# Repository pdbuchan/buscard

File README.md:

# BusCard Project

The illustrated project description is available on the [BusCard GitHub Pages website](https://pdbuchan.github.io/buscard/).

This repository documents information on the BusCard, an IEEE-488 and parallel printer interface for the Commodore 64. The BusCard, and subsequent BusCard II, were manufactured by Batteries Included Ltd. of Toronto, Canada. On my BusCard, the circuit board is labeled "Rev A" and "1983". I used it to provide IEEE-488 functionality to my Commodore 64 in order to use a 4040 disk drive and 8023P printer. It also provides BASIC 4.0 and comes with an assembler and disassembler.

Unlike the BusCard II, the BusCard does not contain any proprietary integrated circuits. As a result, I was able to successfully reverse-engineer it and produce an exact working duplicate. I used EAGLE CAD software for the schematic and circuit board design. All information required to produce it is provided. If you would like to build it, you can send the GERBER files provided here to the manufacturer of your choice. You would only need EAGLE if you wish to change the board layout or circuit.

## License

All of my photographs and EAGLE files are released under [Creative Commons License CC BY-SA](https://creativecommons.org/licenses/by-sa/4.0/). The original BusCard, EPROM content, and user manual are copyright Batteries Included Ltd.

## Repository layout

```text
buscard/
├── README.md
└── docs/
    ├── README.md
    ├── index.html
    ├── .nojekyll
    └── assets/
        ├── buscard.css
        ├── buscard_rev_a_manual.pdf
        ├── schematic.pdf
        ├── cam/
        │   ├── README.md
        │   └── elecrow-gerb274x.cam
        ├── datasheets/
        │   ├── README.md
        │   ├── datasheets.html
        │   ├── 1N4148.pdf
        │   ├── 2N3904.pdf
        │   ├── 2N4401.pdf
        │   ├── 74LS00N.pdf
        │   ├── 74LS04N.pdf
        │   ├── 74LS08N.pdf
        │   ├── 74LS139N.pdf
        │   ├── 74LS21N.pdf
        │   ├── 74LS32N.pdf
        │   ├── 75160B.pdf
        │   ├── 75161B.pdf
        │   ├── 8255AC-5.pdf
        │   ├── 82C55A.pdf
        │   ├── 8-SPST-DIP-Switch.pdf
        │   ├── CK05BX104K.pdf
        │   ├── clip_cable.pdf
        │   ├── clip_receptacle.pdf
        │   ├── female-edge-connector.pdf
        │   ├── micro_clip.pdf
        │   ├── resistor-network.pdf
        │   ├── resistors.pdf
        │   ├── shunt.pdf
        │   └── TMS2564.pdf
        ├── drawings/
        │   ├── README.md
        │   ├── buscard_dimensions.pdf
        │   ├── buscard_dimensions.vsdx
        │   ├── buscard_expansion_port.pdf
        │   ├── buscard_expansion_port.vsdx
        │   ├── buscard_IEEE-488_port.pdf
        │   ├── buscard_IEEE-488_port.vsdx
        │   ├── buscard_parallel_port.pdf
        │   ├── buscard_parallel_port.vsdx
        │   ├── buscard_parts_layout.pdf
        │   ├── buscard_parts_layout.vsdx
        │   ├── buscard_schematic.pdf
        │   ├── new_buscard_dimensions.pdf
        │   └── new_buscard_dimensions.vsdx
        ├── eagle/
        │   ├── README.md
        │   ├── buscard.brd
        │   └── buscard.sch
        ├── eprom/
        │   ├── README.md
        │   ├── buscardv0.9-tms2564.html
        │   ├── buscard_u1_rom_discussion.html
        │   ├── additional-sockets-u13-u14-u15.html
        │   ├── burning_TMS2564_EPROM.docx
        │   ├── burning_TMS2564_EPROM.pdf
        │   ├── buscard_u1_6502_annotated_listing.txt
        │   ├── buscard_u1_rom_discussion.md
        │   ├── additional-sockets-u13-u14-u15.md
        │   └── buscardv0.9-tms2564.bin
        ├── gerber/
        │   ├── README.md
        │   ├── gerber.html
        │   ├── buscard.GBL
        │   ├── buscard.GBO
        │   ├── buscard.GBS
        │   ├── buscard.GML
        │   ├── buscard.GTL
        │   ├── buscard.GTO
        │   ├── buscard.GTS
        │   ├── buscard.TXT
        │   ├── PLEASE_CHAMFER_CARD_EDGES.jpg
        │   └── PLEASE_CONTACT_ME_ABOUT_GOLD_FINGERS.txt
        ├── images/
        │   ├── README.md
        │   ├── orig_gallery.html
        │   ├── new_gallery.html
        │   ├── bottom_cover_inside.jpg
        │   ├── bottom_cover_inside_thumb.jpg
        │   ├── bottom_cover_underside.jpg
        │   ├── bottom_cover_underside_thumb.jpg
        │   ├── bottom.jpg
        │   ├── bottom_of_board_backlit.jpg
        │   ├── bottom_of_board_backlit_thumb.jpg
        │   ├── bottom_thumb.jpg
        │   ├── clips.jpg
        │   ├── clips_thumb.jpg
        │   ├── diodes.jpg
        │   ├── diodes-switch_foil_backlit_top.jpg
        │   ├── diodes-switch_foil_backlit_top_thumb.jpg
        │   ├── diodes-switch_foil_top.jpg
        │   ├── diodes-switch_foil_top_thumb.jpg
        │   ├── diodes_thumb.jpg
        │   ├── expansion_port_backlit1.jpg
        │   ├── expansion_port_backlit1_thumb.jpg
        │   ├── expansion_port_backlit2.jpg
        │   ├── expansion_port_backlit2_thumb.jpg
        │   ├── new_bottom.jpg
        │   ├── new_bottom_thumb.jpg
        │   ├── new_top1.jpg
        │   ├── new_top1_thumb.jpg
        │   ├── new_top2.jpg
        │   ├── new_top2_thumb.jpg
        │   ├── new_top_no_chips1.jpg
        │   ├── new_top_no_chips1_thumb.jpg
        │   ├── new_top_no_chips2.jpg
        │   ├── new_top_no_chips2_thumb.jpg
        │   ├── not_plugged_in.jpg
        │   ├── not_plugged_in_thumb.jpg
        │   ├── photo_buscard_board_bottom_r0.jpg
        │   ├── photo_buscard_board_top_r0.jpg
        │   ├── plugged_in.jpg
        │   ├── plugged_in_thumb.jpg
        │   ├── side_view01.jpg
        │   ├── side_view01_thumb.jpg
        │   ├── side_view02.jpg
        │   ├── side_view02_thumb.jpg
        │   ├── side_view03.jpg
        │   ├── side_view03_thumb.jpg
        │   ├── side_view04.jpg
        │   ├── side_view04_thumb.jpg
        │   ├── side_view05.jpg
        │   ├── side_view05_thumb.jpg
        │   ├── side_view06.jpg
        │   ├── side_view06_thumb.jpg
        │   ├── side_view07.jpg
        │   ├── side_view07_thumb.jpg
        │   ├── side_view08.jpg
        │   ├── side_view08_thumb.jpg
        │   ├── side_view09.jpg
        │   ├── side_view09_thumb.jpg
        │   ├── side_view10.jpg
        │   ├── side_view10_thumb.jpg
        │   ├── side_view11.jpg
        │   ├── side_view11_thumb.jpg
        │   ├── side_view12.jpg
        │   ├── side_view12_thumb.jpg
        │   ├── side_view13.jpg
        │   ├── side_view13_thumb.jpg
        │   ├── top_cover_inside.jpg
        │   ├── top_cover_inside_thumb.jpg
        │   ├── top_foil1.jpg
        │   ├── top_foil1_thumb.jpg
        │   ├── top_no_covers1.jpg
        │   ├── top_no_covers1_thumb.jpg
        │   ├── top_no_covers2.jpg
        │   ├── top_no_covers2_thumb.jpg
        │   ├── top_of_board_backlit.jpg
        │   ├── top_of_board_backlit_thumb.jpg
        │   ├── top_with_bottom_cover1.jpg
        │   ├── top_with_bottom_cover1_thumb.jpg
        │   ├── top_with_bottom_cover2.jpg
        │   ├── top_with_bottom_cover2_thumb.jpg
        │   ├── top_with_cover1.jpg
        │   ├── top_with_cover1_thumb.jpg
        │   ├── top_with_cover2.jpg
        │   └── top_with_cover2_thumb.jpg
        ├── libraries/
        │   ├── README.md
        │   ├── libraries.html
        │   ├── 1N4148.lbr
        │   ├── 2564.lbr
        │   ├── 2N3904_and_2N4401.lbr
        │   ├── 74LS00N.lbr
        │   ├── 74LS04N.lbr
        │   ├── 74LS08N.lbr
        │   ├── 74LS139N.lbr
        │   ├── 74LS21N.lbr
        │   ├── 74LS32N.lbr
        │   ├── 75160AN.lbr
        │   ├── 75161AN.lbr
        │   ├── 8255AC-5.lbr
        │   ├── capacitor-CK05BX104K.lbr
        │   ├── clip-header-MTA02-100.lbr
        │   ├── commodore-card-edges.lbr
        │   ├── dip-switch-DS08.lbr
        │   ├── female-44-pin-edge-connector.lbr
        │   ├── frame.lbr
        │   ├── jumper-header-3.lbr
        │   ├── mystery_plug-MTA04-100.lbr
        │   ├── resistor.lbr
        │   └── resistor-network-sil-G09R.lbr
        └── parts/
            ├── README.md
            ├── new_buscard_bom.xlsx
            └── orig_buscard_parts.xlsx
```

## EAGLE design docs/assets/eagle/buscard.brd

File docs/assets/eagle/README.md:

# EAGLE board and schematic files

| File | Description |
|---|---|
| `buscard.brd` | EAGLE printed circuit board file |
| `buscard.sch` | EAGLE schematic file |

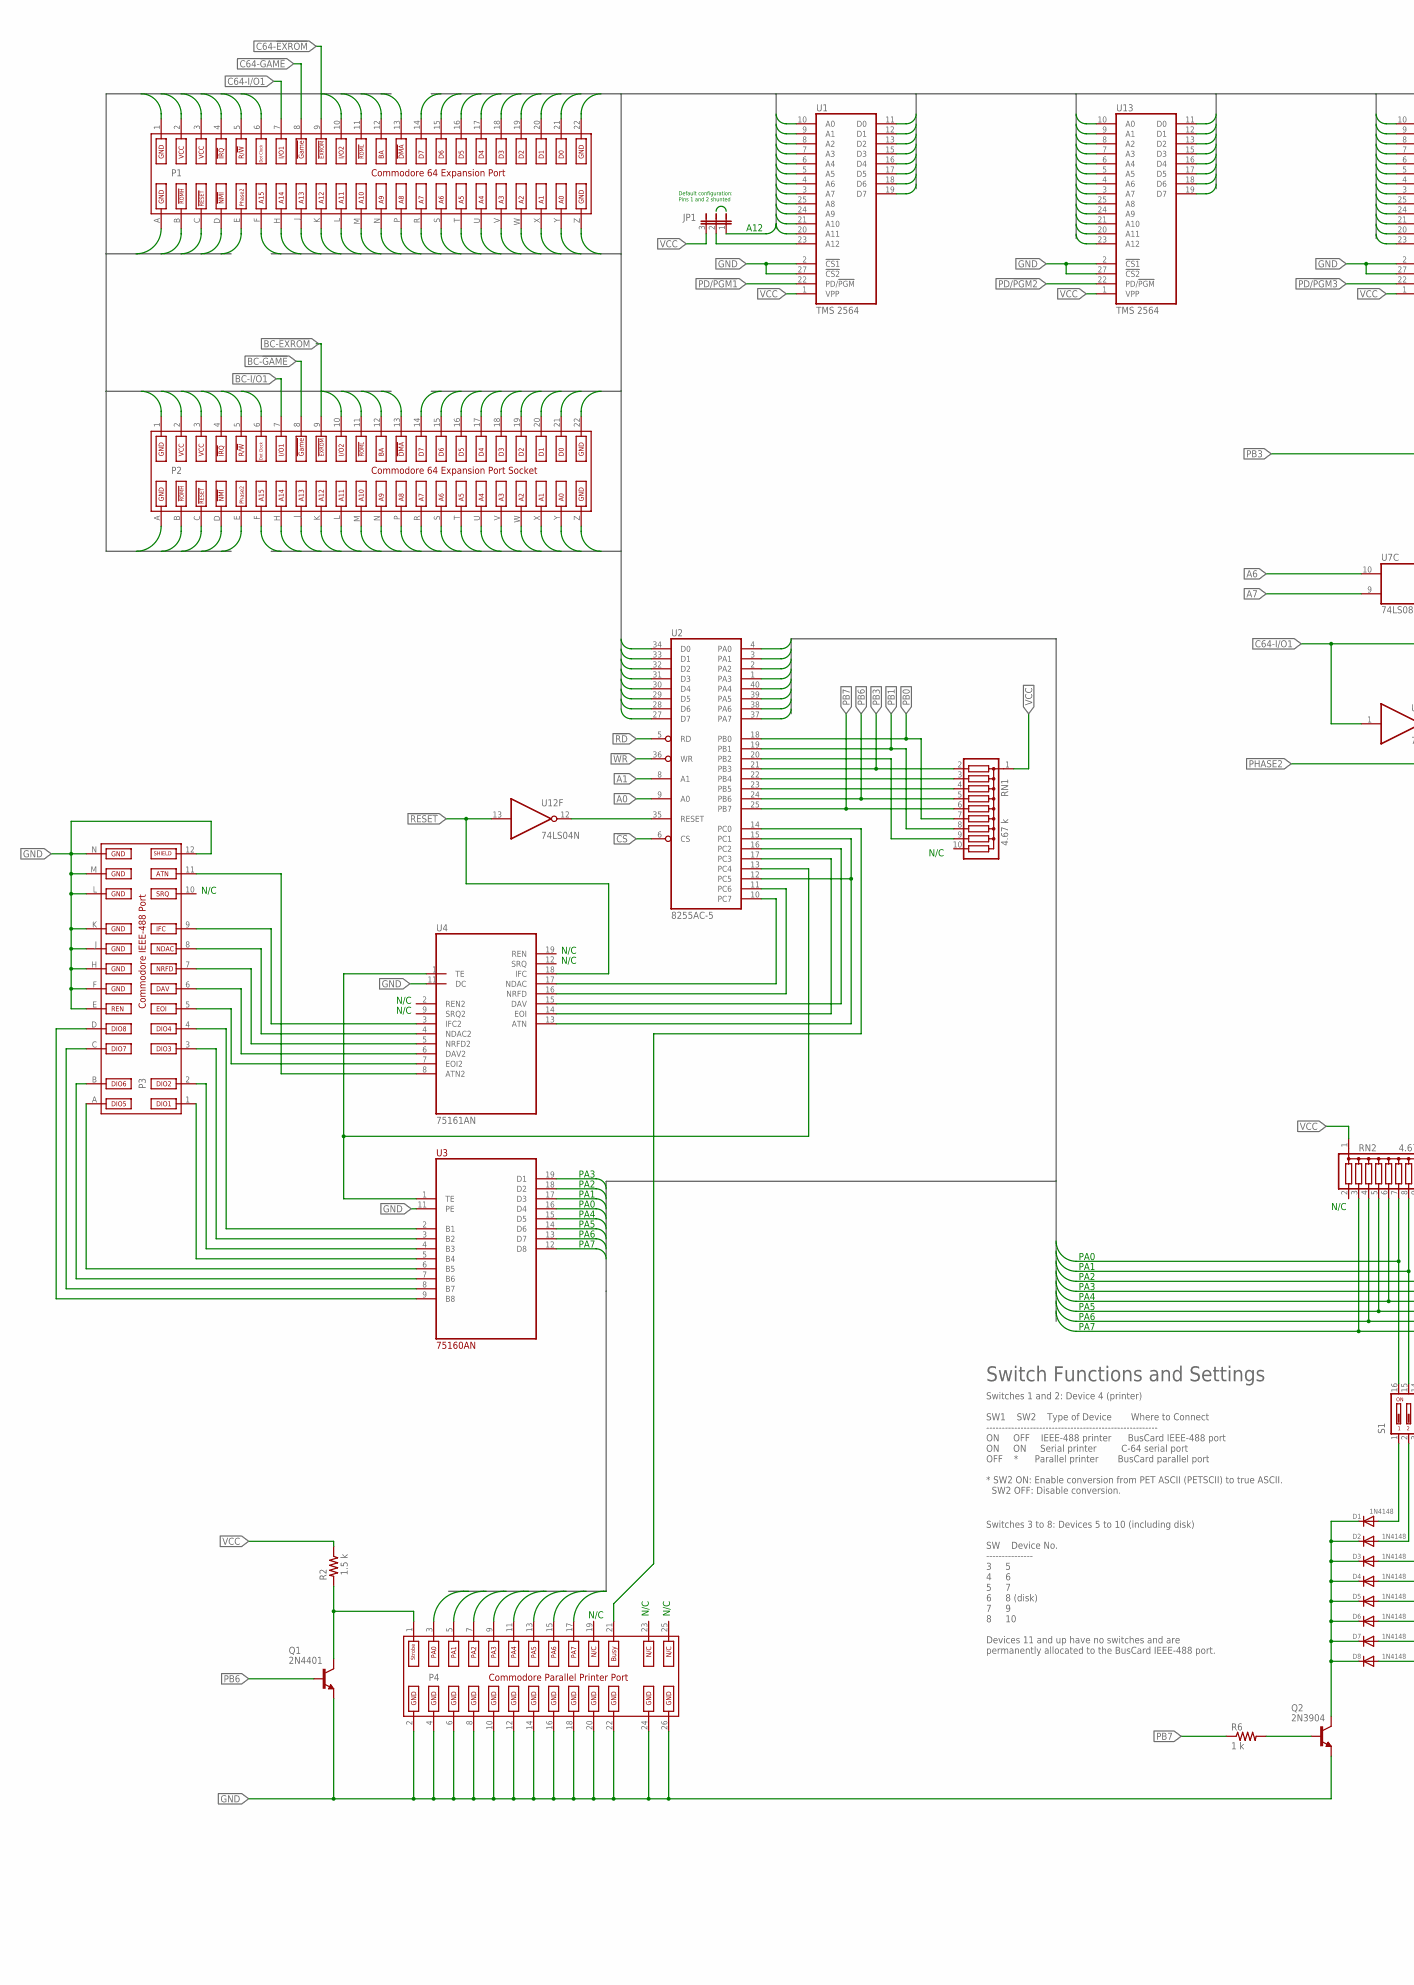
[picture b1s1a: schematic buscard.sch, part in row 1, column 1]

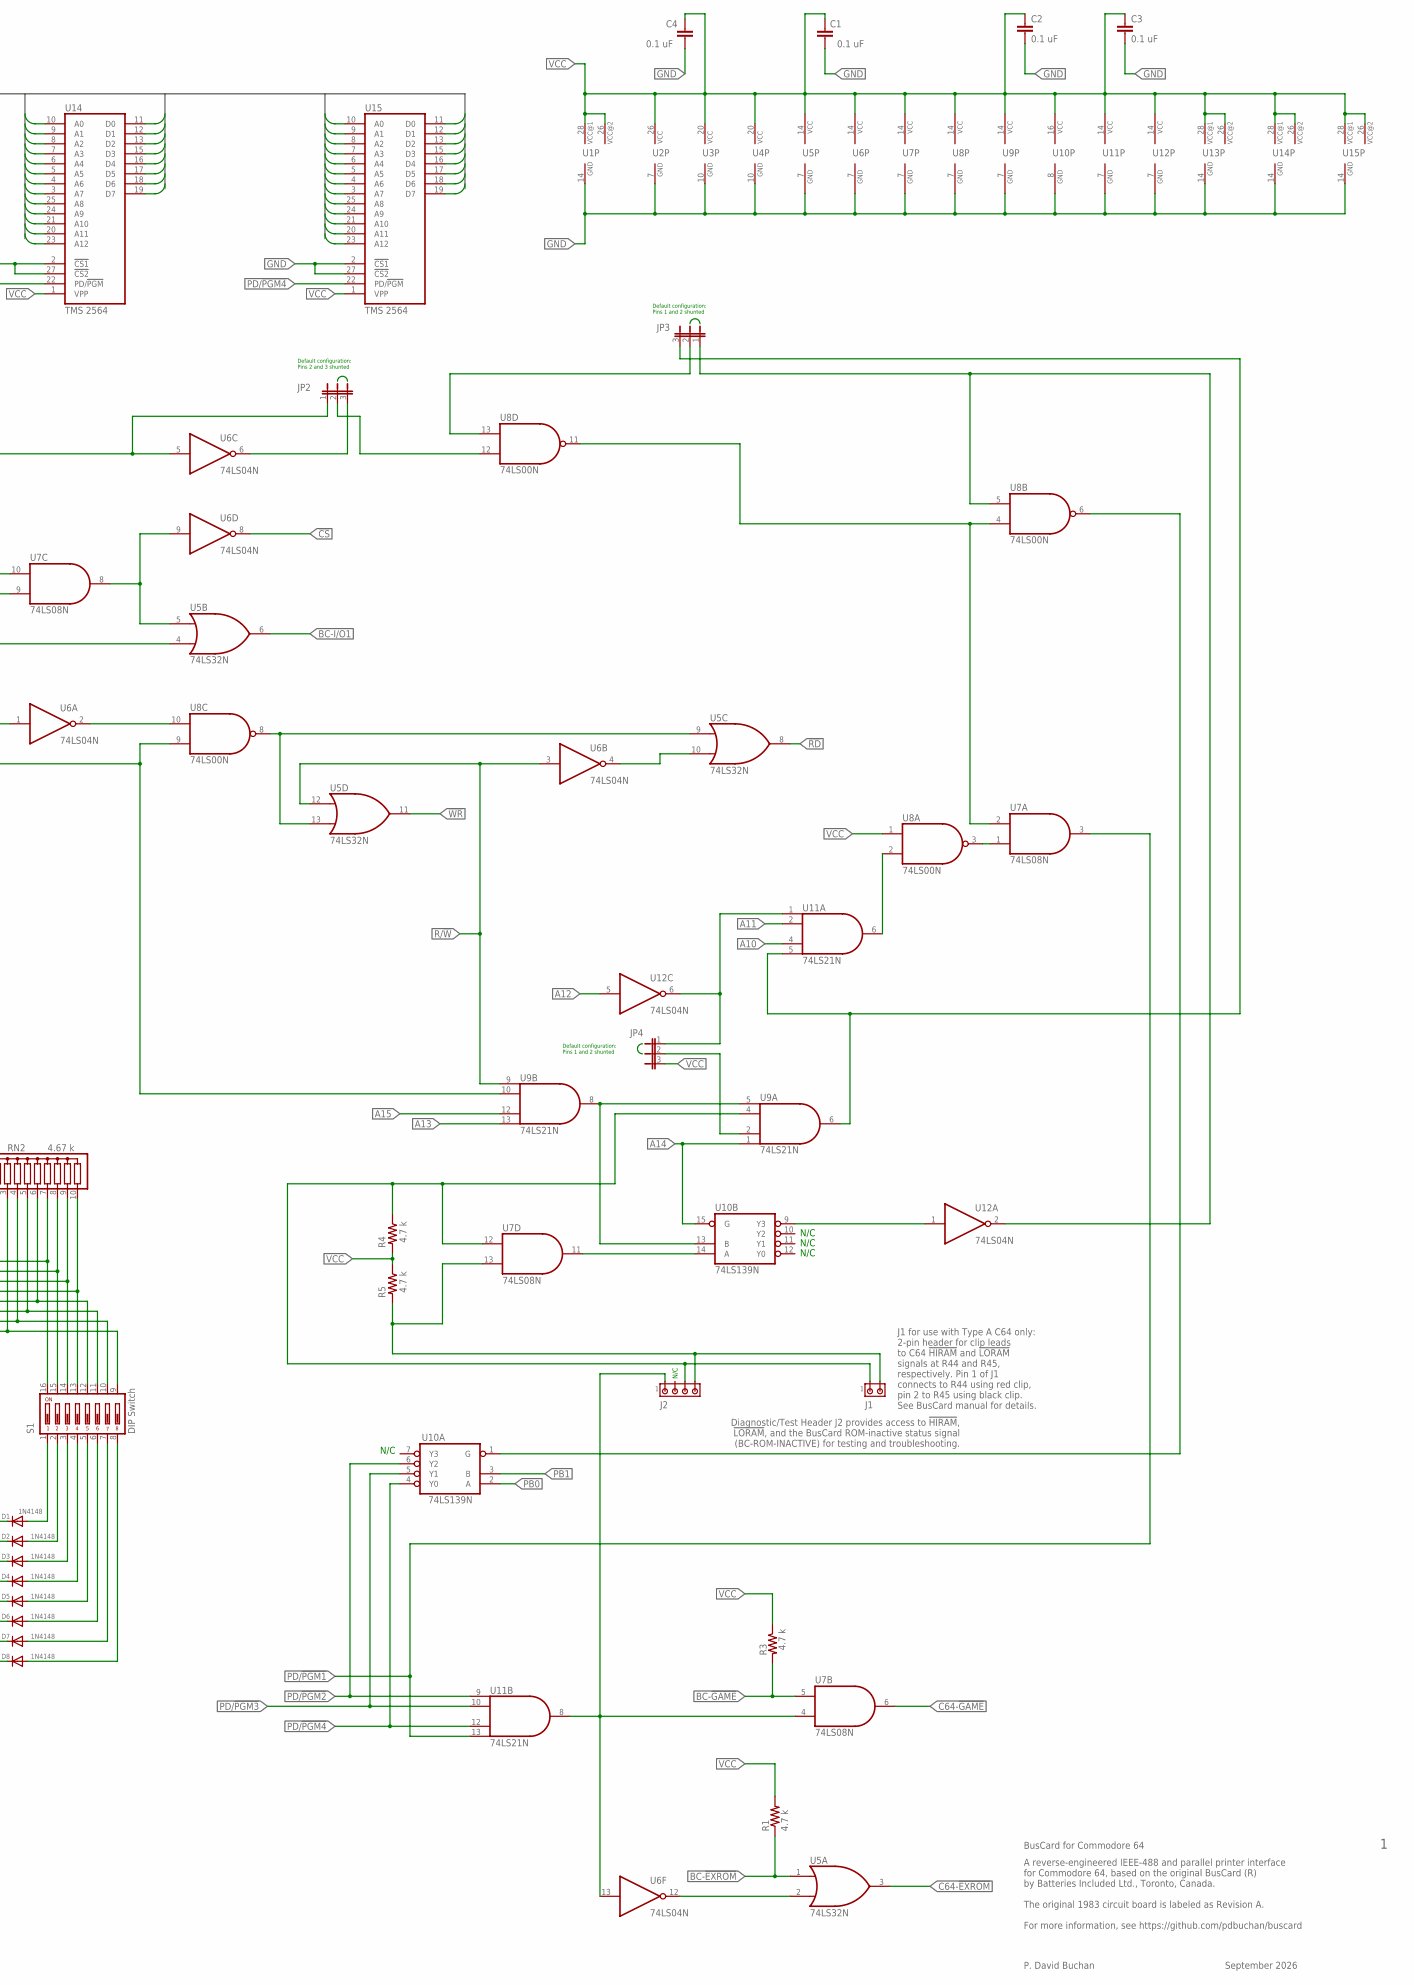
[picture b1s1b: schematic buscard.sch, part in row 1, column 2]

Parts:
C1, C2, C3, C4: 0.1 uF; C075-032X103
D1, D2, D3, D4, D5, D6, D7, D8: 1N4148; DO-1N4148-0.2
J1: MTA02-100; 10X02MTA
J2: MTA04-100; 10X04MTA
JP1, JP2, JP3, JP4: JUMPER-HEADER-3-POSMTA-100; JUMPER-HEADER-3-POS
P1: COMMODORE_64_EXPANSION_PORT_CARD_EDGE
P2: FEMALE_44-PIN_CARD_EDGE_CONNECTOR
P3: COMMODORE_IEEE-488_PORT_CARD_EDGE
P4: Parallel Port; COMMODORE_PARALLEL_PORT_CARD_EDGE
Q1: 2N4401; TO92-EBC
Q2: 2N3904; TO92
R1, R3, R4, R5: 4.7 k; 0207/10
R2: 1.5 k; 0207/10
R6: 1 k; 0207/10
RN1, RN2: 4.67 k; SIL10
S1: DIP Switch; DS-08
U1, U13, U14, U15: TMS 2564; DIL28
U2: 8255AC-5; DIL40
U3: 75160AN; DIL20
U4: 75161AN; DIL20
U5: 74LS32N; DIL14
U6, U12: 74LS04N; DIL14
U7: 74LS08N; DIL14
U8: 74LS00N; DIL14
U9, U11: 74LS21N; DIL14
U10: 74LS139N; DIL16

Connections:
!CS: U2.6 (CS), U6.8 (O)
!DMA: P1.13 (!DMA), P2.13 (!DMA)
!IRQ: P1.4 (!IRQ), P2.4 (!IRQ)
!NMI: P1.D (!NMI), P2.D (!NMI)
!RD: U2.5 (RD), U5.8 (O)
!RESET: P1.C (!RESET), P2.C (!RESET), U4.18 (IFC), U12.13 (I)
!ROMH: P1.B (!ROMH), P2.B (!ROMH)
!ROML: P1.11 (!ROML), P2.11 (!ROML)
!WR: U2.36 (WR), U5.11 (O)
A0: P1.Y (A0), P2.Y (A0), U1.10 (A0), U2.9 (A0), U13.10 (A0), U14.10 (A0), U15.10 (A0)
A1: P1.X (A1), P2.X (A1), U1.9 (A1), U2.8 (A1), U13.9 (A1), U14.9 (A1), U15.9 (A1)
A2: P1.W (A2), P2.W (A2), U1.8 (A2), U13.8 (A2), U14.8 (A2), U15.8 (A2)
A3: P1.V (A3), P2.V (A3), U1.7 (A3), U13.7 (A3), U14.7 (A3), U15.7 (A3)
A4: P1.U (A4), P2.U (A4), U1.6 (A4), U13.6 (A4), U14.6 (A4), U15.6 (A4)
A5: P1.T (A5), P2.T (A5), U1.5 (A5), U13.5 (A5), U14.5 (A5), U15.5 (A5)
A6: P1.S (A6), P2.S (A6), U1.4 (A6), U7.10 (I1), U13.4 (A6), U14.4 (A6), U15.4 (A6)
A7: P1.R (A7), P2.R (A7), U1.3 (A7), U7.9 (I0), U13.3 (A7), U14.3 (A7), U15.3 (A7)
A8: P1.P (A8), P2.P (A8), U1.25 (A8), U13.25 (A8), U14.25 (A8), U15.25 (A8)
A9: P1.N (A9), P2.N (A9), U1.24 (A9), U13.24 (A9), U14.24 (A9), U15.24 (A9)
A10: P1.M (A10), P2.M (A10), U1.21 (A10), U11.4 (I2), U13.21 (A10), U14.21 (A10), U15.21 (A10)
A11: P1.L (A11), P2.L (A11), U1.20 (A11), U11.2 (I1), U13.20 (A11), U14.20 (A11), U15.20 (A11)
A12: JP1.1, P1.K (A12), P2.K (A12), U12.5 (I), U13.23 (A12), U14.23 (A12), U15.23 (A12)
A13: P1.J (A13), P2.J (A13), U9.13 (I3)
A14: P1.H (A14), P2.H (A14), U9.1 (I0), U10.15 (G)
A15: P1.F (A15), P2.F (A15), U9.12 (I2)
ATN: P3.11 (ATN), U4.8 (ATN2)
BA: P1.12 (BA), P2.12 (BA)
BC-!EXROM: P2.9 (!EXROM), R1.1, U5.1 (I0)
BC-!GAME: P2.8 (!GAME), R3.2, U7.5 (I1)
BC-I/O1: P2.7 (I/O1), U5.6 (O)
BC-ROM-INACTIVE: J2.1, U6.13 (I), U7.4 (I0), U11.8 (O)
BUSY: P4.21 (BUSY), U2.14 (PC0)
C64-!EXROM: P1.9 (!EXROM), U5.3 (O)
C64-!GAME: P1.8 (!GAME), U7.6 (O)
C64-I/O1: P1.7 (I/O1), U5.4 (I0), U6.1 (I)
CLIP1: J1.2, J2.4, R5.2, U7.13 (I1)
CLIP2: J1.1, J2.3, R4.1, U7.12 (I0), U9.4 (I2)
D0: P1.21 (D0), P2.21 (D0), U1.11 (D0), U2.34 (D0), U13.11 (D0), U14.11 (D0), U15.11 (D0)
D1: P1.20 (D1), P2.20 (D1), U1.12 (D1), U2.33 (D1), U13.12 (D1), U14.12 (D1), U15.12 (D1)
D2: P1.19 (D2), P2.19 (D2), U1.13 (D2), U2.32 (D2), U13.13 (D2), U14.13 (D2), U15.13 (D2)
D3: P1.18 (D3), P2.18 (D3), U1.15 (D3), U2.31 (D3), U13.15 (D3), U14.15 (D3), U15.15 (D3)
D4: P1.17 (D4), P2.17 (D4), U1.16 (D4), U2.30 (D4), U13.16 (D4), U14.16 (D4), U15.16 (D4)
D5: P1.16 (D5), P2.16 (D5), U1.17 (D5), U2.29 (D5), U13.17 (D5), U14.17 (D5), U15.17 (D5)
D6: P1.15 (D6), P2.15 (D6), U1.18 (D6), U2.28 (D6), U13.18 (D6), U14.18 (D6), U15.18 (D6)
D7: P1.14 (D7), P2.14 (D7), U1.19 (D7), U2.27 (D7), U13.19 (D7), U14.19 (D7), U15.19 (D7)
DAV: P3.6 (DAV), U4.6 (DAV2)
DIO1: P3.1 (DIO1), U3.5 (B4)
DIO2: P3.2 (DIO2), U3.4 (B3)
DIO3: P3.3 (DIO3), U3.3 (B2)
DIO4: P3.4 (DIO4), U3.2 (B1)
DIO5: P3.A (DIO5), U3.6 (B5)
DIO6: P3.B (DIO6), U3.7 (B6)
DIO7: P3.C (DIO7), U3.8 (B7)
DIO8: P3.D (DIO8), U3.9 (B8)
DOT_CLOCK: P1.6 (DOT_CLOCK), P2.6 (DOT_CLOCK)
EOI: P3.5 (EOI), U4.7 (EOI2)
GND: C1.1, C2.2, C3.2, C4.2, P1.1 (GND), P1.22 (GND), P1.A (GND), P1.Z (GND), P2.1 (GND), P2.22 (GND), P2.A (GND), P2.Z (GND), P3.12 (SHIELD), P3.E (REN), P3.F (GND), P3.H (GND), P3.J (GND), P3.K (GND), P3.L (GND), P3.M (GND), P3.N (GND), P4.2 (GND), P4.4 (GND), P4.6 (GND), P4.8 (GND), P4.10 (GND), P4.12 (GND), P4.14 (GND), P4.16 (GND), P4.18 (GND), P4.20 (GND), P4.22 (GND), P4.24 (GND), P4.26 (GND), Q1.E, Q2.3 (E), U1.2 (!CS1), U1.14 (GND), U1.27 (!CS2), U2.7 (GND), U3.10 (GND), U3.11 (PE), U4.10 (GND), U4.11 (DC), U5.7 (GND), U6.7 (GND), U7.7 (GND), U8.7 (GND), U9.7 (GND), U10.8 (GND), U11.7 (GND), U12.7 (GND), U13.2 (!CS1), U13.14 (GND), U13.27 (!CS2), U14.2 (!CS1), U14.14 (GND), U14.27 (!CS2), U15.2 (!CS1), U15.14 (GND), U15.27 (!CS2)
I/O2: P1.10 (I/O2), P2.10 (I/O2)
IFC: P3.9 (IFC), U4.3 (IFC2)
unnamed: JP2.3, U6.6 (O)
unnamed: JP2.2, U8.12 (I0)
unnamed: JP3.2, U8.13 (I1)
unnamed: U8.6 (O), U10.1 (G)
unnamed: U6.2 (O), U8.10 (I1)
unnamed: U5.10 (I1), U6.4 (O)
unnamed: U5.9 (I0), U5.13 (I1), U8.8 (O)
unnamed: U9.5 (I3), U9.8 (O), U10.13 (B)
unnamed: U8.2 (I1), U11.6 (O)
unnamed: JP4.2, U9.2 (I1)
unnamed: JP4.1, U11.1 (I0), U12.6 (O)
unnamed: JP3.3, U9.6 (O), U11.5 (I3)
unnamed: U7.1 (I0), U8.3 (O)
unnamed: U10.9 (Y3), U12.1 (I)
unnamed: U7.11 (O), U10.14 (A)
unnamed: D1.A, S1.1
unnamed: U5.2 (I1), U6.12 (O)
unnamed: D2.A, S1.2
unnamed: D3.A, S1.3
unnamed: D4.A, S1.4
unnamed: D5.A, S1.5
unnamed: D6.A, S1.6
unnamed: D7.A, S1.7
unnamed: JP1.2, U1.23 (A12)
unnamed: D8.A, S1.8
unnamed: U2.10 (PC7), U4.17 (NDAC)
unnamed: Q2.2 (B), R6.2
unnamed: D1.C, D2.C, D3.C, D4.C, D5.C, D6.C, D7.C, D8.C, Q2.1 (C)
unnamed: U2.11 (PC6), U4.16 (NRFD)
unnamed: RN1.3, U2.22 (PB4)
unnamed: RN1.4, U2.23 (PB5)
unnamed: RN1.9, U2.20 (PB2)
unnamed: U2.16 (PC2), U4.15 (DAV)
unnamed: U2.35 (RESET), U12.12 (O)
unnamed: U7.2 (I1), U8.4 (I0), U8.11 (O)
unnamed: JP3.1, U8.5 (I1), U12.2 (O)
unnamed: U5.5 (I1), U6.9 (I), U7.8 (O)
unnamed: U2.17 (PC3), U4.14 (EOI)
unnamed: U2.12 (PC5), U2.15 (PC1), U4.13 (ATN)
NDAC: P3.8 (NDAC), U4.4 (NDAC2)
NRFD: P3.7 (NRFD), U4.5 (NRFD2)
PA0: P4.3 (PA0), RN2.7, S1.16, U2.4 (PA0), U3.16 (D4)
PA1: P4.5 (PA1), RN2.8, S1.15, U2.3 (PA1), U3.17 (D3)
PA2: P4.7 (PA2), RN2.9, S1.14, U2.2 (PA2), U3.18 (D2)
PA3: P4.9 (PA3), RN2.10, S1.13, U2.1 (PA3), U3.19 (D1)
PA4: P4.11 (PA4), RN2.6, S1.12, U2.40 (PA4), U3.15 (D5)
PA5: P4.13 (PA5), RN2.5, S1.11, U2.39 (PA5), U3.14 (D6)
PA6: P4.15 (PA6), RN2.4, S1.10, U2.38 (PA6), U3.13 (D7)
PA7: P4.17 (PA7), RN2.3, S1.9, U2.37 (PA7), U3.12 (D8)
PB0: RN1.7, U2.18 (PB0), U10.2 (A)
PB1: RN1.8, U2.19 (PB1), U10.3 (B)
PB3: JP2.1, RN1.2, U2.21 (PB3), U6.5 (I)
PB6: Q1.B, RN1.5, U2.24 (PB6)
PB7: R6.1, RN1.6, U2.25 (PB7)
PD/!PGM1: U1.22 (PD/!PGM), U7.3 (O), U11.13 (I3)
PD/!PGM2: U10.6 (Y2), U11.9 (I0), U13.22 (PD/!PGM)
PD/!PGM3: U10.5 (Y1), U11.10 (I1), U14.22 (PD/!PGM)
PD/!PGM4: U10.4 (Y0), U11.12 (I2), U15.22 (PD/!PGM)
PHASE2: P1.E (PHASE2), P2.E (PHASE2), U8.9 (I0), U9.10 (I1)
R/!W: P1.5 (R/!W), P2.5 (R/!W), U5.12 (I0), U6.3 (I), U9.9 (I0)
STROBE: P4.1 (STROBE), Q1.C, R2.2
TE: U2.13 (PC4), U3.1 (TE), U4.1 (TE)
VCC: C1.2, C2.1, C3.1, C4.1, JP1.3, JP4.3, P1.2 (VCC), P1.3 (VCC), P2.2 (VCC), P2.3 (VCC), R1.2, R2.1, R3.1, R4.2, R5.1, RN1.1, RN2.1, U1.1 (VPP), U1.26 (VCC), U1.28 (VCC), U2.26 (VCC), U3.20 (VCC), U4.20 (VCC), U5.14 (VCC), U6.14 (VCC), U7.14 (VCC), U8.1 (I0), U8.14 (VCC), U9.14 (VCC), U10.16 (VCC), U11.14 (VCC), U12.14 (VCC), U13.1 (VPP), U13.26 (VCC), U13.28 (VCC), U14.1 (VPP), U14.26 (VCC), U14.28 (VCC), U15.1 (VPP), U15.26 (VCC), U15.28 (VCC)

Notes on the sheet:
N/C
PA3
PA2
PA1
PA0
PA4
PA5
PA6
PA7
P. David Buchan
BusCard for Commodore 64
A reverse-engineered IEEE-488 and parallel printer interface for Commodore 64, based on the original BusCard (R) by Batteries Included Ltd., Toronto, Canada. The original 1983 circuit board is labeled as Revision A. For more information, see https://github.com/pdbuchan/buscard
Diagnostic/Test Header J2 provides access to !HIRAM!, !LORAM!, and the BusCard ROM-inactive status signal (BC-ROM-INACTIVE) for testing and troubleshooting.
September 2026
Switch Functions and Settings
Switches 1 and 2: Device 4 (printer) SW1 SW2 Type of Device Where to Connect ------------------------------------------------------- ON OFF IEEE-488 printer BusCard IEEE-488 port ON ON Serial printer C-64 serial port OFF * Parallel printer BusCard parallel port * SW2 ON: Enable conversion from PET 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
Switches 3 to 8: Devices 5 to 10 (including disk) SW Device No. --------------- 3 5 4 6 5 7 6 8 (disk) 7 9 8 10 Devices 11 and up have no switches and are permanently allocated to the BusCard IEEE-488 port.
J1 for use with Type A C64 only: 2-pin header for clip leads to C64 !HIRAM! and !LORAM! signals at R44 and R45, respectively. Pin 1 of J1 connects to R44 using red clip, pin 2 to R45 using black clip. See BusCard manual for details.
A12
Default configuration: Pins 1 and 2 shunted
Default configuration: Pins 2 and 3 shunted

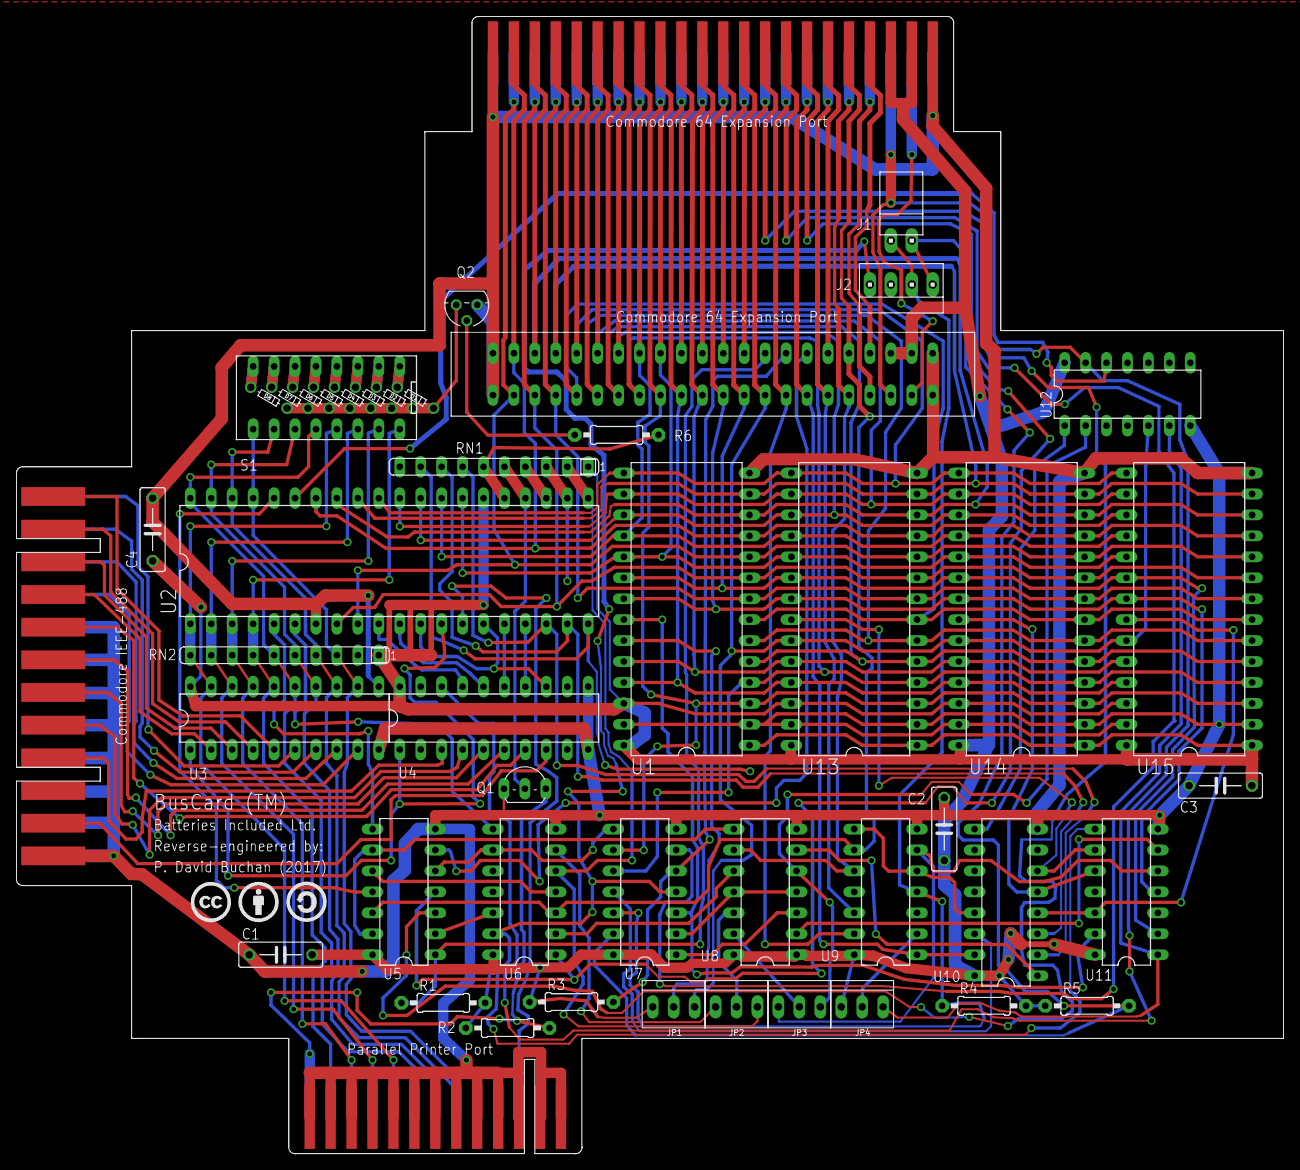
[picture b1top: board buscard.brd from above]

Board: 2 copper layers, 153.7 x 137.9 mm, 48 parts (0 on the bottom side), 122 nets.

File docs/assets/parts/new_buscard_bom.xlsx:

Bill of Materials for Reverse-Engineered BusCard (Revision A)
My Part I.D. | Qty. | Vendor | Vendor I.D. | Technology | Description
Circuit Board | 1 | Elecrow | PCB Prototyping | ENIG | 2-layer, 2-sided, 0.063" (1.6 mm) thick, blue, no stencil, ENIG, card-edges cha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
U1, U13-15 | 1 | ebay | TMS2564 | TMS 2564 | 65,536-bit, Ultraviolet-Erasable, Electrically Programmable Read-Only Memory (E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
U2 | 1 | Newark | 79K6034 | CP82C55A-5Z | 8-bit Programmable Peripheral Interface, 40-Pin, 5 Mhz
U3 | 1 | Newark | 60K6925 | 75160BN | IEEE-488 GPIB Octal Bus Transceiver
U4 | 1 | Newark | 62K3469 | 75161BN | IEEE-488 GPIB Octal Bus-Management and Data-Transfer Transceiver
U5 | 1 | Newark | 08F7225 | 74LS32N | Quadruple 2-Input Positive-OR Gates
U6, U12 | 2 | Newark | 60K6850 | 74LS04N | Hex Inverting Gates
U7 | 1 | Newark | 60K6852 | 74LS08N | Quadruple 2-Input Positive-AND Gates
U8 | 1 | Newark | 60K6847 | 74LS00N | Quadruple 2-Input Positive-NAND Gates
U9, U11 | 2 | Newark | 08F6993 | 74LS21N | Dual 4-Input Positive-AND Gates
U10 | 1 | Newark | 08F6771 | 74LS139N | Dual 1-of-4 Decoder/Demultiplexer
Q1 | 1 | Newark | 08N8113 | 2N4401 | NPN Transistor, 600 mA, 40 V
Q2 | 1 | Newark | 08N8111 | 2N3904 | NPN Transistor, 200 mA, 40 V
D1-8 | 8 | Newark | 58K9570 | 1N4148 | Small Signal Diode, 200 mA, 100 V
R1, R3, R4-5 | 4 | Newark | 38K0376 | 4.7 kΩ Resistor | Resistor, 4.7 kΩ, 1/4 watt, 5% tolerance
R2 | 1 | Newark | 38K0340 | 1.5 kΩ Resistor | Resistor, 1.5 kΩ, 1/4 watt, 5% tolerance
R6 | 1 | Newark | 38K0327 | 1 kΩ Resistor | Resistor, 1 kΩ, 1/4 watt, 5% tolerance
RN1, RN2 | 2 | Newark | 32K9264 | 4.67 kΩ Resistor Network | SIL Resistor Network, 4.67 kΩ, 10 Pins, 9 Resistors, Bussed Arrangement
C1-4 | 4 | Newark | 87F4662 | CK05BX104K | Ceramic Capacitor, 0.1 μF, 50 V, Radial, 10% tolerance
S1 | 1 | Newark | 40T8914 | 8 SPST DIP Switch | 8 SPST, DIP Switch, Raised Slide
P2 | 1 | Newark | 42K9934 | Female Card-Edge Connector | 44-contact (2-rows of 22 contacts), 0.1" (2.54 mm) contact spacing (pitch), 0.2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
XU2 | 1 | Newark | 16M3455 | IC Socket | DIP, 40-Pin (2x20), 0.1" (2.54 mm) contact spacing (pitch), 0.6" (15.24 mm) row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
XU1, XU13-15 | 4 | Newark | 52K3643 | IC Socket | DIP, 28-Pin (2x14), 0.1" (2.54 mm) contact spacing (pitch), 0.6" (15.24 mm) row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
XU3-4 | 2 | Newark | 17C2233 | IC Socket | DIP, 20-Pin (2x10), 0.1" (2.54 mm) contact spacing (pitch), 0.3" (7.62 mm) row 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
XU10, XS1 | 2 | Newark | 17C2229 | IC Socket | DIP, 16-Pin (2x8), 0.1" (2.54 mm) contact spacing (pitch), 0.3" (7.62 mm) row s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
XU5-9, XU11-12 | 7 | Newark | 17C2226 | IC Socket | DIP, 14-Pin (2x7), 0.1" (2.54 mm) contact spacing (pitch), 0.3" (7.62 mm) row s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
XRN1-2 | 2 | Newark | 52K3253 | SIP Socket for Resistor Network | SIP, 10-Pin (1x10), 0.1" (2.54 mm) contact spacing (pitch)
J2 | 1 | Newark | 90F5641 | 4-position Connector Header | Wire-to-board connector header, 4-position, 1-row, straight, 0.1" (2.54 mm) con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
JP1-4 | 4 | Newark | 90F4251 | 3-position Connector Header | Wire-to-board connector header, 3-position, 1-row, straight, 0.1" (2.54 mm) con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
J1 | 1 | Newark | 90F5638 | 2-position Connector Header | Wire-to-board connector header, 2-position, 1-row, 90-degrees, 0.1" (2.54 mm) c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
Clip Receptacle | 1 | Newark | 52K3585 | 2-position Connector Receptacle | Wire-to-board connector receptacle, 2-position, 1-row, straight, 0.1" (2.54 mm)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
Clip (red) | 1 | Newark | 13H6565 | Spring-loaded Test Clip | Test Clip, Spring-Loaded, Hook, Red, 3 A, 43.43 mm Overall Length
Clip (black) | 1 | Newark | 48F5003 | Spring-loaded Test Clip | Test Clip, Spring-Loaded, Hook, Black, 3 A, 43.43 mm Overall Length
Clip Cable | 1 | Newark | 67R9277 | Ribbon Cable | Ribbon Cable, Round Conductor, Flat, Zippable, 16 Conductors (peel off 2; you c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
JP1-4 | 4 | Newark | 55H0426 | 2-position Shunt | Shunt, female, 2-position, 0.1" (2.54 mm) contact spacing (pitch), 0.347" (8.81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
